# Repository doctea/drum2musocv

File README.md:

# drum2musocv

* Note that I am on the way to replacing this functionality in my system with the [Microlidian](https://github.com/doctea/Microlidian) project instead.

* A USB MIDI interface, originally for adapting the [MidiMuso Orac CV-12](http://midimuso.co.uk/index.php/cv-12/) to be used as a drum machine (mapping GM drum channel/notes and providing triggerable ADSR envelopes), but now with many added features.

* ~~In active development...~~ very likely to be bugs or things that can be very much improved.  Check back for updates or contact me if you're trying to use this!

* Currently targets [Arduino Zero clones](https://www.banggood.com/Geekcreit-SAMD21-M0-Module-32-bit-ARM-Cortex-M0-Core-Development-Board-p-1176168.html)/[Seeeduino Cortex M0+ boards](https://www.seeedstudio.com/Seeeduino-Cortex-M0-p-4070.html), originally started out on an Arduino Uno (probably possible to make it work on a Uno again or other MCUs).

* **Drum pitch mapping** allows you to play the CV-12 using external drum pads, or eg take advantage of FL Studio's note-naming in the piano roll.

* When it isn't receiving an **external clock input**, runs off its own **internal clock** at the last detected BPM.

* Implements **5 triggerable envelopes** (or **9** with two Oracs) with AHDSR (attack, hold, decay, sustain, release) stages, output on the CCs that the midimuso uses for its CV outputs so they can be used as envelopes.  Default mapped to the 'Cymbal Crash 2', 'Cymbal Splash', 'Vibra-slap', 'Ride Bell' and 'Ride Cymbal 1' GM drum notes for input (with MIDI control to map to any of the drum triggers or note-ons on the Harmony/MIDI channels), outputting on the muso's CV outs #1, #2, #3, #4 and #5 respectively (via midimuso CC 1, 7, 11, 71 and 74 - with reconfiguring could be used as triggerable CC envelopes for any device).

* Envelopes can now be set to loop per-envelope ie become freerunning LFOs with envelope-like control.  Retriggerable + inverted mode for each.

* **Visual feedback**: Indicates triggers and envelope levels via a 16-LED RGB Neopixel strip using the FastLED library on pin 9.

* Includes a **control surface preset for FL Studio** to make controlling the general, Euclidian and envelope settings easy and saveable/recallable per-project.

* Has a 19-track **Euclidian rhythm generator** with optional mutation mode, so you can play with your synth without loading a DAW.  Can configure tracks on/off, change mutation settings, etc, from DAW.  In mutation mode, mutates the rhythm every 2 bars, with options on mutation.
 * Could also be used to add generative/mutating Euclidian rhythms to any MIDI device (drum machine etc) if reconfigured to use different output note mappings.

* **Plays bass, chords/arped chords and additional pitched midi channels** from Euclidian patterns, and with **auto-generated chord changes and inversions**.  Allows **tied notes**.
 * If notes are played in via MIDI determine which notes to use for arpeggiation/chords.  Plays chords and additional midi channels with auto-generated chord changes and inversions.

* Plays a **"drum fill"** for the last bar of every phrase by mutating the Euclidian rhythms.

* Temporary hack: uses the pitch bend output instead of the CV output that corresponds to CC 74, because mine seems to be broken.  (could use this in future to add an extra envelope/CV out or LFO output..)

* **Optionally echoes the MIDI output back to the host**, so that you can record the rhythms for re-use or to route to softsynths or other MIDI devices.

* Outputs **4xClock triggers** using a CD74HC4067 multiplexor (5ms latency between outputs if multiple triggered simultaneously) - every beat, every upbeat, every bar, every phrase.  Uses Arduino data pins 2,3,4,5 to set the multiplexor output.

* Can use a single midimuso in mode 0B or 2B, or two midimusos via a midi splitter, one in mode 0B and one in 2A

# Controls

 - Two buttons, button 1 on pin A0 and button 2 on pin 8
 - Press button 1 = cycle through demo modes (standby -> Euclidian -> Euclidian with mutation -> random -> Experimental Euclidian mutation mode that mutates more things and also keeps track of the virtual drummer's limbs to avoid playing impossible rhythms -> back to start)
 - When in a Euclidian mode:
   - Press button 2 = enable/disable Euclidian generation (to shut it up but to keep mode)
   - Hold button 2 for > 2 seconds & release = reset Euclidian patterns to initial default. (LEDs will light up red momentarily)
 - When any button is pressed or released, LEDs will light up violet, current mode indicated by a blue LED on first row of pixels, autoplaying status indicated by red/green on last pixel)

# Routing of features

A diagram to help me understand how everything is routed:-

# Using single midimuso-cv board

  - Configure mode by setting `MUSO_MODE` define in Config.h to `MUSO_MODE_0B` (10xGate, 5xCV Envelope) or `MUSO_MODE_2B` (7xGate, 5xCV Envelope, 2xPitch, 2xPitch Gate)

# Using multiple midimuso-cv boards

  - Configure mode by setting `MUSO_MODE` define in Config.h to `MUSO_MODE_0B_AND_2A` (10xGate, 5xCV Envelope, 2xPitch, 4xPitch Envelope)
  - Now supports running two midimuso-cv boards via MIDI splitter (NOT chained):
    - Board 1 in mode 0B (10 triggers* + 5 envelopes)
    - Board 2 in mode 2A (2 pitch outputs + 4 extended envelopes)
  - Extended envelopes can have parameters set using appropriate CC's on **Channel 11**
    - by default they trigger on notes on MIDI channels 1 + 2 (root pitch / pad pitch)
  - Check the `RELAY_PROGRAM_CHANGE` define in order to enable/protect setting of muso modes when you want to update its mode (allows/prevents program change messages being passed on)
  - *: Because of a problem with the MidiMuso-CV12 in mode 0B (A Gate 1 is also triggered on Channel 1 Pitch input), Kick moves to Stick and Stick is disabled, reducing us to 10 triggers instead of 11.  But does mean the old 'Kick' output can be used as gate for MIDI channel 1.

# MIDI parameters

(TODO: incomplete docs, need to add the notes corresponding to the Muso triggers for bass drum, snare, ch/oh etc, CCs corresponding to the envelope parameters, and other settings eg clock sync)

 - see the [CHANNEL_AND_CC_LIST.txt](CHANNEL_AND_CC_LIST.txt) document for a complete autogenerated list of the existing mappings
 - and [MIDI_CC_TABLE.md](MIDI_CC_TABLE.md) for a slightly better organised autogenerated MIDI CC list

## MIDI Inputs

| MIDI type   | MIDI channel | MIDI number    | Purpose                    |
| ----------  | ------------ | -------------- | -------------------------- | 
| Note on/off | 1,2,3,4      | any            | Output notes to corresponding channel, trigger envelope if assigned |
| Note on/off | 10           | Cymbal Crash 2 | Trigger envelope on CV 1 (default, change by assigning trigger)  |
| Note        | 10           | Cymbal Splash  | Trigger envelope on CV 2 (default, change by assigning trigger)  |
| Note        | 10           | Vibra Slap     | Trigger envelope on CV 3 (default, change by assigning trigger)  |
| Note        | 10           | Ride Bell      | Trigger envelope on CV 4 (default, change by assigning trigger)  |
| Note        | 10           | Ride Cymbal    | Trigger envelope on CV 5* (default, change by assigning trigger)  |
| Note        | 10           | ..GM drums..   | Trigger Muso triggers      |
| CC          | 10           | 32 to 48       | Enable/disable Euclidian track |
| Note+CC etc | 8            | any            | Bass synth - Resend on channel 4 |
| Note        | 9            | any            | Bass synth - Euclidian track arpeggiates held chord on chan 2+3 (see below) |

## MIDI Outputs

| Type         	| MIDI channel | MIDI number   | Purpose |
| ------------- | ------------ | ------------- | ------- |
| Notes/CC/etc  | 1     | any | Output to Muso Pitch 1 |
| Notes/CC/etc  | 2     | any | Output to Muso Pitch 2 |
| Notes/CC/etc  | 3     | any | Output to bitbox keys |
| Notes/CC/etc 	| 4 	| any | Output to bass synth | TODO: forward modulation as aftertouch/velocity/modwheel etc |
| Notes   	| 11    | 36-51 (C2-D#3) | 'shadow' copy of notes sent to midimuso, starting at C2 so they work with default bitbox pads |
| Notes 	| 16 	| 60-70 (C4-?) | outputs to MIDI Muso CV-12, gates for drum triggers |
| CV + pitch 	| 1 	| 1,7,11,71,74+pitch | outputs to MIDI Muso, CV/pitch outputs for envelopes |

* *actually this currently outputs on the Pitch Bend output, as my Muso output seems to be broken - configure this by changing `MUSO_USE_PITCH_FOR` in Drums.h 

# Requirements

 - Use the Seeeduino Zero board profile so that Serial has printf() - install boards from URL https://files.seeedstudio.com/arduino/package_seeeduino_boards_index.json and add contents of the included [boards.txt](boards.txt) to the end of eg `C:\Users\\<YOUR_USERNAME>\AppData\Local\Arduino15\packages\Seeeduino\hardware\sam\1.8.1\boards.txt`.  You can then edit the USB device name and IDs in that file.
 - Can be used in conjunction with USBMidiKlik (https://github.com/TheKikGen/USBMidiKliK) to provide USB MIDI, or can use native USB on boards that support it.  (hasn't been tested on board without native USB for a while so this is likely broken currently)
 - Uses the FortySevenEffects MIDI library and FastLED library (with alternative experimental support for the Adafruit NeoPixel library).
 - Stock DebounceEvent uses delay(), so need to apply patch from https://github.com/arjanmels/debounceevent/commit/c26419a5a2eb83c07bcb69e8073cecd7453c53bf.patch to fix stutter when buttons are pressed

# FL Studio DAW Control Surface preset

 - *Euclidian settings.fst* is an FL Studio Patcher preset for controlling the Euclidian settings (screenshot below).
 - [deprecated] *Drum2MusoCV - Bamblweeny.fst* is an FL Studio MIDI Out preset for controlling the drum triggers and envelope settings - now included in separate tab

# Hardware/demos

[Testing modular + mutating Euclidian sequencer #2 video](https://www.youtube.com/watch?v=taRN2wLEkPA)

 - **TODO:** document the hardware used
  - buttons on which pins / how wired?
  - MIDI DIN on TX, how wired?
  - header output for pixels, how wired?
    - data on pin 9
  - clock outputs, how wired?

----

# Issues

 - Problems with midimuso pitch gates missing note-off messages when stopping everything, when a lot of notes need to be told to go off.  workaround by defining WORKAROUND_MISSED_NOTEOFFS in MidiOutput.hpp to insert short delay()s sometimes when sending a lot of messages during douse_all_trigger() calls.  Tried increasing TX buffer size but makes no difference, this seems to fix things in 99% of cases altho still sometimes misses the messages..
 - Rapidly pressing 'stop' in DAW retriggers notes -- think due to it causing a tick

----

# TODO / future plans + ideas

 - 'Acid' harmony output mode, with note ties and automation acid line generation (maybe take some inspiration from [Aciduino](https://github.com/midilab/aciduino) and [endless acid banger](https://github.com/vitling/acid-banger))

 - Separate the harmony inputs, so you can specify different lines to play for each harmony output, including 'only when note held' stuff

 - Check that chord/scale generation is actually working to produce valid output - wondering if i'm accidentally basing the entire scale off the chord root?

 - Rename the project to something catchier and more reflective of its abilities

 - Refactor to make it easier to add new drum and harmony outputs
   - and modes to re-output drum triggers on appropriate GM Drum notes, for controlling MIDI drum machines (would start at MidiOutput.hpp:fire_trigger and get_muso_pitch_for_trigger for this)

 - Song section mode for song structures, eg build up, break, intense, chilled, ..
   - 'intensity' / 'sparesness' controls over mutation?

 - Different banks of starting rhythms so we don't get bored to tears of 4/4 kick...
   - preprogramme some and have them selectable?
   - or cleverly randomise them somehow like mutations?

 - Replace DebounceEvent library with one that doesn't need patching

 - Make CC config options to able to enable/disable so the CV outputs can be used as CCs, envelopes (done!) or LFOs per-project

 - LFOs

 - TODO: Make euclidian sequences changeable on the fly/configurable, saveable

 - Add more physical buttons to provide greater control over modes  

 - Make a KiCad circuit / PCB / panel to integrate LEDs and outputs behind a panel
   - tiny OLED and rotary encoder would be interesting, to tweak settings from panel without faffing with DAW
   - as would accepting parameter changes via i2c connection from controllers like the [F8R](https://michigansynthworks.com/products/8m-fader-bank-with-cv-i2c-and-midi), like I've just become aware some Eurorack modules do (eg Disting)
 
 - Replace DebounceEvent library with one that doesn't need patching

 - Cut bass by kick option

 - Completely edit euclidian track parameters over MIDI... with feedback to control surface in daw for saving?  Trigger all outputs simultaneously/groups if have two recording groups

 - Shadow triggers with MIDI to trigger Bitbox.  output options - global/per track - muso/bitbox/both.  always/random/alternate/pattern (+euclidian)?  add this to fire_trigger & douse_trigger?
	- more broadly this is turning into a need to have more of a structure for outputs, for sending to host/midi over multiple channels and can be turned on and off easily
	- Allow to configure the octave-shifted melody/pad outputs on Channel 3:
		- configuration of octave shift
		- option to arpeggiate on None / Channel 2 / Channel 3 / Both
		- option to play full-chord / arp / root-only on Channel 3

 - Bitbox recording mode? ie send all triggers necessary to record a sample.  buttons to trigger recording?

 - More 'predictable' random streams... like use 'different' random streams for picking numbers at different stages of mutation, so that can add feature to mutate more tracks simultaneously but keep the existing patterns the same
	- so keep the selection of patterns chosen to change the same, each pattern's mutations the same -- actually not sure if i'm on the right track here.  come back when less tired!

 - More envelope stages (delay?)

 - Other 'modules' to trigger other devices with CV via relays (ie circuit bent stuff).  Extra CVs/triggers direct from the Arduino?  Shitty sample recorder/player?!

 - Hi-hat/crash choke (cut open hat gate when pedal hat is triggered?)

 - Funkier colours / colour blending fx for the pixels

 - Save config options (RGB settings, envelope settings, euclidian patterns etc) to the flash memory and allow configuration via sysex / CCs.
	 - Started adding this, but isn't supported on SAMD platforms, so aborted (untested code remains)
	 - support FRAM over SPI, or saving to SD card?
	 
 - Add extra envelope output on the pitch bend output (but currently using this to replace my broken output C6/cc74)

### Done list

 - Make the envelopes triggerable by any trigger, not just MIDI
	- with toggleables in the control surface using formula conrtoller to combine checkboxes with knob values
 - Can put envelopes into LFO modes: looping and inverted
	- lost ability to modulate from previous version, but looping and inverted is still decent right?  and have run out of ccs to control the envelopes for the envelopes
 - Euclidian fills on last bar of phrase.  Multiply the track parameters to increase/decrease density?
 - Make euclidian sequences work off midi clock, fix any bpm issues.
 - Make BPM guesser only work off the last 4 steps, to handle live changes of tempo better (done, but still needs 3 beats before it becomes accurate...?)
 - Fix problem where BPM guesser doesn't reset when stopped? - done i think
 - Fix problem with lights staying on when sequencer stopped? - seems to be resolved
 - First beat is missing when starting playback.. seems to think it starts from step 1?. -done for both playback and internal, i think !
 - Echo euclidian output back to host so that we can record the midi or reuse it on other instruments etc
 - Better syncing of envelopes to midi clock ?
 - Make modulation configurable per-stage, eg only wobble during release
 - BUG: there is a 'click' at end of envelope releases
 - TODO: find out whether an envelope is being held open or whether the ringing i'm getting is actually a problem with module
 - Not convinced the envelopes are entirely working as intended so need to check & fix this
 - Make modulation sync work again
 - Route MIDI on specfic input channel to specific output channel, so can play eg Neutron through same interface
 - LEDs for indication of mode
 - Shadow triggers with MIDI to trigger Bitbox
   - done: basic shadow of triggers+envelopes on the default bitbox pad trigger notes, sending on channel 11
 - Latency/flam/swing on euclidian tracks.  Adjust the euclidian loop to check a copy of received_ticks that is adjusted by the appropriate latency
        - ie if latency is set to -6, then remove 6 from received_ticks before tests is on bar etc
                - gonna need to restructure slightly for this, or maybe just make some defines for testing like IS_ON_BAR(ticks), IS_ON_STEP(ticks)?
                - will need to turn the loops inside out and iterate over tracks before checking if theyre on beat
 - Set some of the envelopes to act as envelopes synchronous with some of the triggers, for applying modulation to hits or notes.
 - Tied notes, per-track or just for bass.  to do this do we just avoid sending note off for last note until new note has been sent..? off/always/random/pattern?
 - Rough implementation of the melody rhythm randomness from the [endless acid banger](https://github.com/vitling/acid-banger))
 - Make Euclidian bass capable of changing root note / arpeggiate / chord sequences
   - features to do this.  currently arps over held chord
   - make this so can switch between modes...
 - Support multiple MidiMuso-CVs - one for max pitch/cv, one for pitch outputs+envelopes
   - DONE: finish adding control panel for the extra 4 envelopes
     - DONE: added controls for 2 extra envelopes
 
----

# Feedback / Contributions
 
Would love if people found a use for this, so if you are interested at all in this project then it would be great to hear from you!  [Let me know](mailto:doctea@gmail.com) what you're interested in using the project for, what doesn't work, or any other questions or feedback you may have...

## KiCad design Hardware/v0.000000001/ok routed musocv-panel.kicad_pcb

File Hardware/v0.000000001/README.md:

Definitely not to be used!  These are my first attempts at designing a front panel, and a PCB to fit that would host midimuso output jacks alongside RGB LEDs for indication.  Mocked up are spaces for an OLED screen, should I ever manage to get that to work nicely.

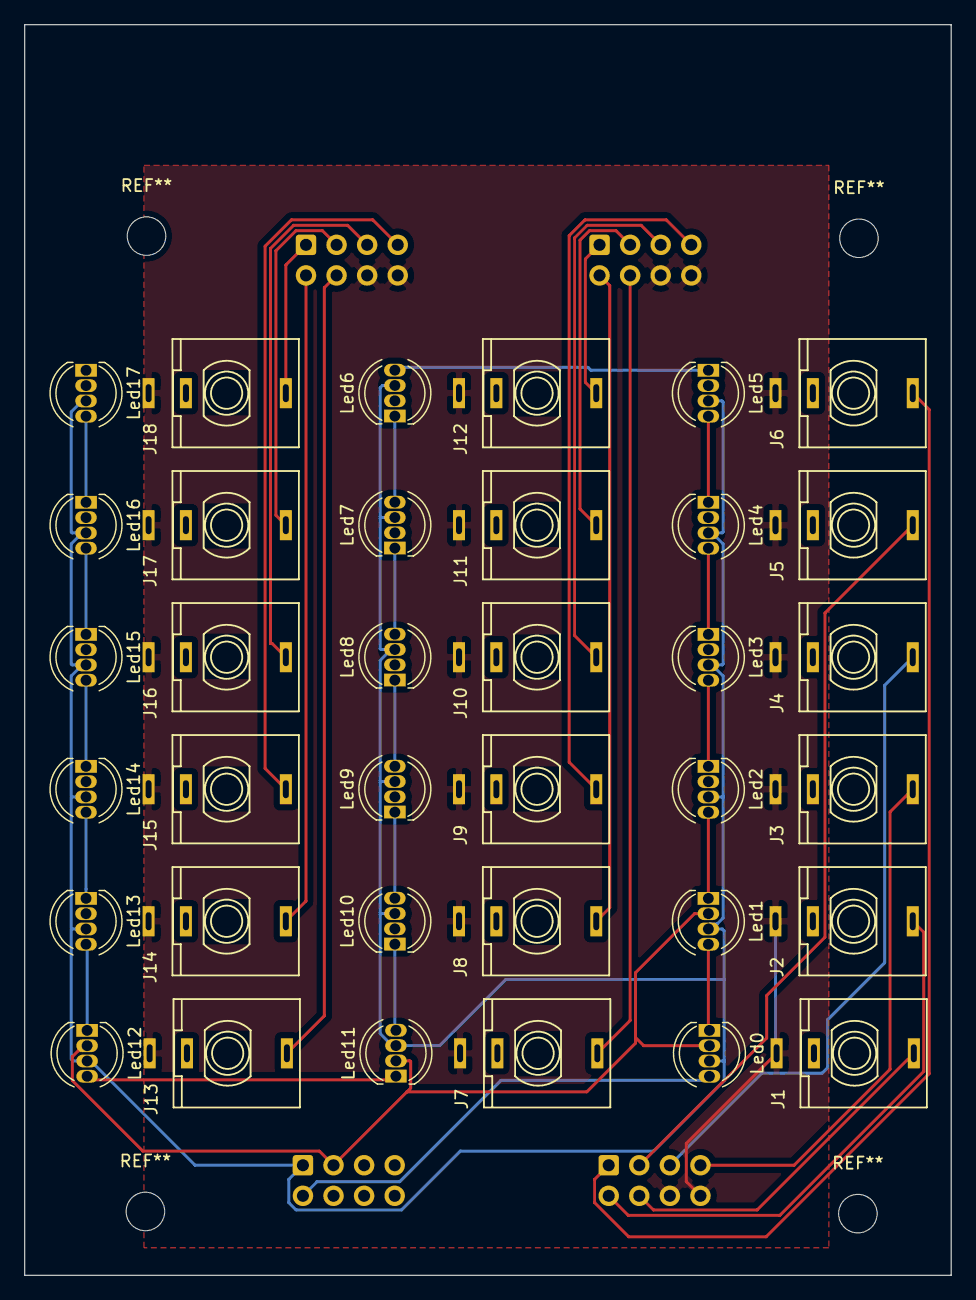
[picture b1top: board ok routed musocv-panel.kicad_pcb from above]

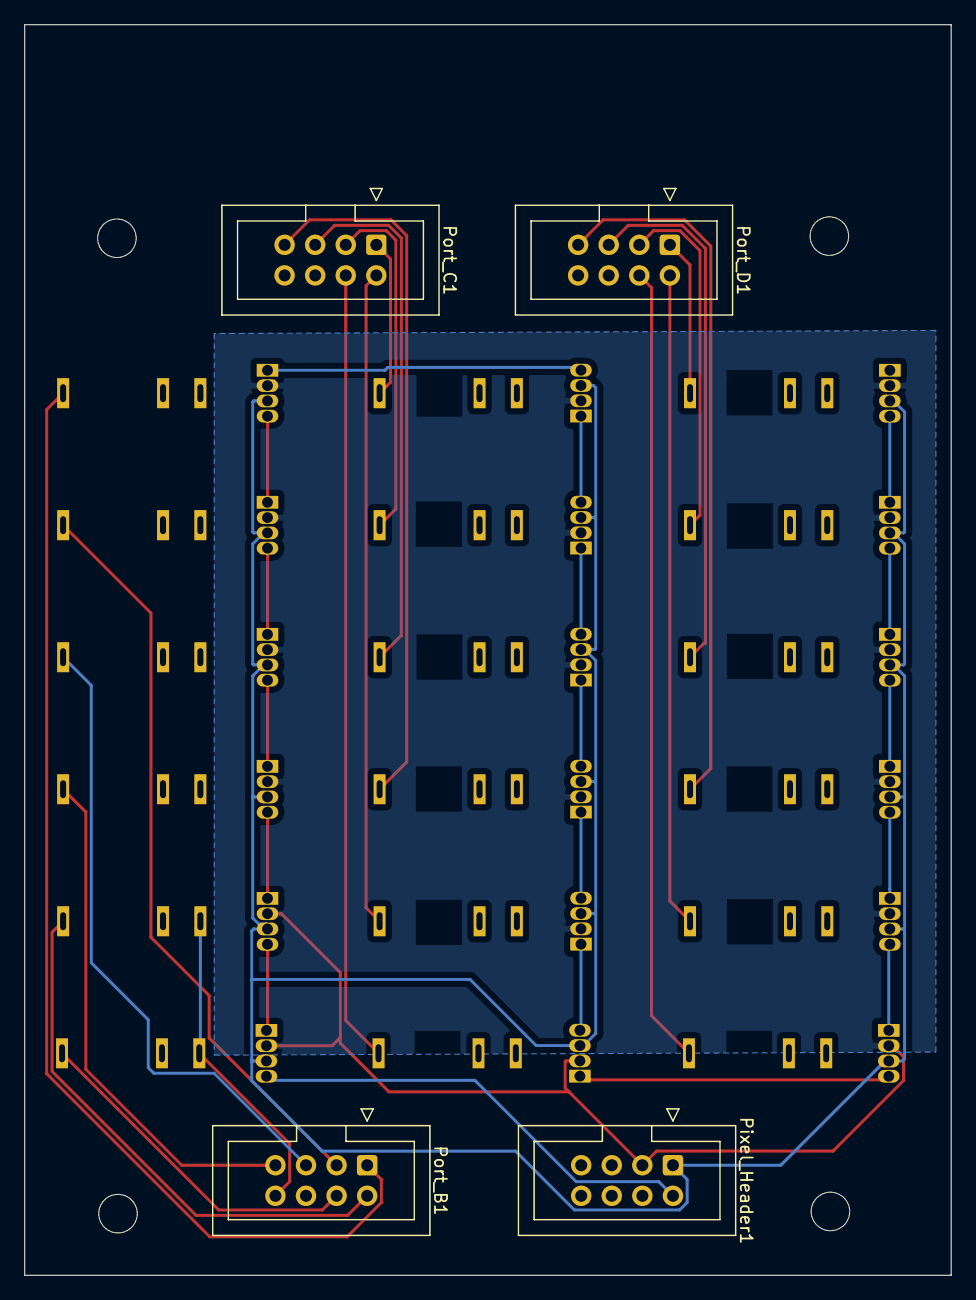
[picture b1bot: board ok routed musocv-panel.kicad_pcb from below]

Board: 2 copper layers, 77.0 x 103.9 mm, 40 parts (4 on the bottom side), 39 nets.

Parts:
J1, J2, J3, J4, J5, J6, J7, J8, J9, J10, J11, J12, J13, J14, J15, J16, J17, J18: fuzzySI_thonkiconn; thonkiconn_fuzzySi
Led0, Led1, Led2, Led3, Led4, Led5, Led6, Led7, Led8, Led9, Led10, Led11, Led12, Led13, Led14, Led15, Led16, Led17: NeoPixel_THT; LED_D5.0mm-4
Pixel_Header1: Conn_02x04_Odd_Even; IDC-Header_2x04_P2.54mm_Vertical
Port_B1: Conn_02x04_Odd_Even; IDC-Header_2x04_P2.54mm_Vertical
Port_C1: Conn_02x04_Odd_Even; IDC-Header_2x04_P2.54mm_Vertical
Port_D1: Conn_02x04_Odd_Even; IDC-Header_2x04_P2.54mm_Vertical

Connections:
GND: J1.1, J2.1, J3.1, J4.1, J5.1, J6.1, J7.1, J8.1, J9.1, J10.1, J11.1, J12.1, J13.1, J14.1, J15.1, J16.1, J17.1, J18.1, Port_B1.6, Port_B1.8, Port_C1.6, Port_C1.8, Port_D1.6, Port_D1.8
unnamed: Led0.1, Led1.4
unnamed: Led1.1, Led2.4
unnamed: Led2.1, Led3.4
unnamed: Led3.1, Led4.4
unnamed: Led4.1, Led5.4
unnamed: Led5.1, Led6.4
unnamed: Led6.1, Led7.4
unnamed: Led7.1, Led8.4
unnamed: Led8.1, Led9.4
unnamed: Led10.1, Led11.4
unnamed: Led9.1, Led10.4
unnamed: Led11.1, Led12.4
unnamed: Led12.1, Led13.4
unnamed: Led13.1, Led14.4
unnamed: Led14.1, Led15.4
unnamed: Led15.1, Led16.4
unnamed: Led16.1, Led17.4
Pixel_Data: Led0.4, Pixel_Header1.2
Pixel_GND: Led0.2, Led1.2, Led2.2, Led3.2, Led4.2, Led5.2, Led6.2, Led7.2, Led8.2, Led9.2, Led10.2, Led11.2, Led12.2, Led13.2, Led14.2, Led15.2, Led16.2, Led17.2, Pixel_Header1.3
Pixel_VDD: Led0.3, Led1.3, Led2.3, Led3.3, Led4.3, Led5.3, Led6.3, Led7.3, Led8.3, Led9.3, Led10.3, Led11.3, Led12.3, Led13.3, Led14.3, Led15.3, Led16.3, Led17.3, Pixel_Header1.1
Port_B_0: J6.3, Port_B1.1
Port_B_1: J5.3, Port_B1.3
Port_B_2: J4.3, Port_B1.5
Port_B_3: J3.3, Port_B1.7
Port_B_4: J2.3, Port_B1.2
Port_B_5: J1.3, Port_B1.4
Port_C_0: J12.3, Port_C1.1
Port_C_1: J11.3, Port_C1.3
Port_C_2: J10.3, Port_C1.5
Port_C_3: J9.3, Port_C1.7
Port_C_4: J8.3, Port_C1.2
Port_C_5: J7.3, Port_C1.4
Port_D_0: J18.3, Port_D1.1
Port_D_1: J17.3, Port_D1.3
Port_D_2: J16.3, Port_D1.5
Port_D_3: J15.3, Port_D1.7
Port_D_4: J14.3, Port_D1.2
Port_D_5: J13.3, Port_D1.4

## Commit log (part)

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2020-08-15 First commit -- after a lot of dumb mistakes and mucking around, actually works to translate the gates in 0X0B mode to general midi channel 10!
2020-08-16 Velocity-sensitive, crude envelope generated on midimuso CC7 when triggered on 57/67 (A4/G5)
2020-08-16 ADSR envelope... non-working at all now heh
2020-08-16 think its bloody working !! commit before proving = tidyup...
2020-08-16 two envelope channels working i think!
2020-08-22 minor fix
2020-08-22 Better define overall MIDI clock sync
2020-08-22 Envelopes seem to be working ok now, maybe some weirdness at times but overall seems good
2020-08-22 tis working better generally, awful bugs fixed, sync lfo isnt quite right tho
2020-09-05 prototype of using a neopixel type strip to indicate activity
2020-09-05 Triggers and envelopes shown on LED strip
2020-09-14 Improved RGB output, added 2 more envelopes, added FL Studio preset to control envelop settings.
2020-09-14 little tidy-up
2020-10-04 don't miss commands when pressing play in daw now -- was neopixel interferring.... made the neopixel update code only update the leds if there has been a change, which seems to have alleviated the pr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
2020-10-08 button on pin A0 to switch in and out of 'demo mode' (triggers random hits, handy for testing synth without loading DAW), moved global variable declarations around
2020-11-20 works on Seeeduino Cortex M0+
2020-11-20 comment
2020-12-29 experimental Euclidian rythym generator and a few other tweaks, need to test this with real midi clock
2020-12-30 WIP, improving clock/bpm handling... syncs with external clock ok, but doesnt track it properly if it is changed. also time when left to its own devices isnt right
2020-12-30 bpm finder works much better, sequences start from correct place
2020-12-30 ignore first false button press + remove some debugging
2020-12-30 better
2021-01-01 envelopes work again, now synced to the new clock internal or external
2021-01-01 tracked missing new UI file for button handling
2021-01-02 clock pulse now sent every beat; slight code tidy up; euclidian pattern XORing (unverified if working like expected!)
2021-01-02 added (and then disabled, because the SAMD platforms dont support it) UNTESTED saving of bpm & patterns to eeprom
2021-01-02 tidy up so that it 'might' work on proper platform
2021-01-02 tidy up and fix a few glitches (all envelopes can be used now, modes are better-behaved when switching between, etc)
2021-01-03 envelopes now work again (even when external clock isn't running...). internal clock now runs when havent had input for a while and continues running even after receiving triggers so that envelopes g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
2021-01-03 attempting to fix envelope sync... currently non-working ...
2021-01-03 ok, that should be envelope rates and stage parameters synced with clock rate solved..! TODO: fix the modulation too
2021-01-09 envelope Sync Ratio Hold-Decay and Sustain-Release now make sense again
2021-01-09 CC control over number of clock ticks it takes to trigger a clock tick, FL DAW template updated to match (CC 111)
2021-01-23 fix silly typo with start/continue handler. change midi handling to omni, in prep for having neutron connected too. tidy up some redundant comments
2021-01-23 hack to use pitch bend output instead of cc74 since mine appears to be broken; pass through channel 8 to channel 2 (for daisychaining my Neutron)
2021-01-27 kill triggers when switching modes, drop default envelope release time to half, cut euclidian note length to half a beat
2021-01-27 internal tidyup to make some things saner
2021-01-30 bass sequence stuff moved into own file, uses defined scale and wraps by octaves correctly. improve serial debugging in Euclidian and Bass (turn on/off with defines)
2021-01-30 fix a couple of things with BPM counter (correct beat / bar numbers)
2021-01-31 more little improvements, need to make the bass options configurable + controllable..
2021-01-31 SLOW via adafruit_gfx library..
2021-01-31 not working too well
2021-02-01 can switch between graphics libs with define
2021-02-05 committed multiple gfx library versions while trying to figure out which is easiest / best
2021-02-06 nonworking or very slow screen attempts
2021-02-06 chords held on midi channel 9 will be arpeggiated on the bass output
2021-02-07 simple rename ahead of making a class out of the channel handler
2021-02-07 tidy up&comment, play bass automatically again, turn off when receiving autobass - need a way to disable it from DAW now
2021-02-08 echo bass notes back to host
2021-02-11 Replace previous Euclidian control surface with a full Patcher preset with MIDI Out configured too
2021-02-11 midi cc's to only play bass when chords held, select arp mode, select demo mode
2021-02-13 fixed file extension
2021-02-13 Euclidian sequences are now song-position dependent, with 127 'banks' to select from
2021-02-14 added more Euclidian mutation options
2021-02-14 explicitly include Euclidian.h, for readability
2021-02-14 more flexible / predictable euclidian seed setting, i think
2021-02-15 CC-switchable mutate mode with a 'total randomise' mode
2021-02-20 stray character
2021-02-20 should be able to have euclidian sequences of more than 16 steps - should be in use on the envelope tracks but might be some bugs there
2021-02-26 typo
2021-02-27 fills only by option, patterns always reset if mutate or fills are enabled, send song start on clock reset, output 24 PPQN MIDI clock
2021-02-27 easier to configure auto arp/progression in code
2021-02-28 extra ideas / docs
2021-02-28 updated diagram
2021-02-28 sort of working harmony refactor, but somehow wrong ChannelState object is being addressed?!
2021-02-28 compiles
2021-03-01 chords playing through melody channel fine
2021-03-01 plays melody using arp over bass playing root, using auto chord progression. still need to refactor the chord progress/arp stuff
2021-03-01 marked readme with what this branch is for
2021-03-07 not really working very well...
2021-03-07 working for 4 clock triggers (downbeat, upbeat, bar, phrase), 5m per trigger, seems working and stable!
2021-03-07 enable/disable by define
2021-03-07 fix clock triggers not triggering
2021-03-12 correct notes played for chord now i think!
2021-03-12 ok think this does play correct notes for chords... (nothing actually changed since last commit?)
2021-03-14 maybe not entirely fixed or sane harmony handling, but much better and several bugs fixed
2021-03-14 some more bugs squashed
2021-03-22 Added some scales, 'improved' inversion logic
2021-03-26 can configure+switch on the fly the midi output channels (also means you can turn them off by setting to 0), melody offset is now one higher than it was before
2021-03-26 added then disabled non-working arping over current chord (need to store this in harmony when triggered and then reuse?)
2021-03-27 euclidian duration 0 douses after a half-step, better kill notes i think?
2021-03-28 force-kill envelope outputs from douse_all_triggers
2021-03-31 stab at supporting midimuso mode 2B, not working as expected, and currently crashes...
2021-04-01 woop i think triggers and everything now match up properly when in 2B mode! todo: sensible program change message handling, ie dont resend same values, to avoid it resetting all the time
2021-04-01 default to NOT relaying program change messages so we dont keep overwriting the midimuso configuration
2021-04-03 2x muso outputs work, doubling up on the bass and melody
2021-04-04 bass and melody now fire from independent Euclidian patterns
2021-04-04 added note that have to use the Seeeduino board config to enable printf on Serial
2021-04-04 couple tidyups
2021-04-05 working a bit better..
2021-04-05 Numerous fixes for vscode intellisense sanity, and general fixes for some things that had broken
2021-04-05 tying notes for porta works..?
2021-04-06 configuiable tie_on for bass output
2021-04-07 default snare pattern is now sane, added screenshot of the current Euclidian settings control panel
2021-04-08 removed a load of redundant commented code etc, moved a few things round
2021-04-10 start of hacky script to build MIDI CC table from the source code
2021-04-10 proper md now?
2021-04-10 update midi cc table builder
2021-04-10 commented CCs
2021-04-11 removed BASS_ARP as can now set arp mode on 2xharmony outputs individually, fixed a problem with note-offs when in chord mode, added workaround for some stuck note on stop failures on midimuso cv-12
2021-04-11 hide some debug
2021-04-14 improve comments and rearranged defines, to make easier to add forthcoming envelope-on-trigger doubling
2021-04-14 tracked .vscode settings (not portable to other setups though presuambly?)
2021-04-15 removed useless file
2021-04-15 untested, should allow per-envelope setting to fire alongside harmony output firing (todo: for pass-thru midi note-on/offs too)
2021-04-18 updated control surface, envelopes kills notes when changing trigger
2021-04-18 updated euclidian settings flstudio control surface again, Envelopes is now on another tab and laid out better
2021-04-18 melody mode and octave offset controls for output#2 (Pad Root)
2021-04-18 improve readme
2021-04-18 link to arduino zero boards
2021-04-20 better direct-midi handling i think?
2021-04-25 mentioned acid-banger again in readme
2021-04-25 use full range of Sustain in envelopes -- allows now to do short blips with envelopes
2021-04-25 just changed colour in daw template
2021-04-29 tracked early fumbles into designing a panel/PCB
2021-05-03 extended envelopes for running multiple midi musos -- one in mode 0B for 11 triggers + 5 envelopes, one in mode 2A for 2 pitches + 4 envelopes
2021-05-03 testing -- better ignore program change messages i think...
2021-05-03 works with two midimusocv boards, configurable envelopes for the pitches, updated images/docs/daw template
2021-05-09 workaround for midimuso-cv12 problem where notes received on channel 1 also trigger the A Gate 1 output when in mode 0B.
2021-05-16 added UI controls for the final two envelopes
2021-05-28 added warning when loop takes longer than one midi tick; disabled some debug output
2021-11-12 optimise gate lookup because why not
2021-11-12 oops, initialise trigger table too
2021-11-13 removed some debug output
2021-11-13 experimental extra modes for lfo mode, inverted and modulated... opens up a new world!
2021-11-27 better handling of out-of-range pitches
2021-11-27 triggers have different led colours and this is refleced in the button colours in the FL template
2021-12-08 default density plays the default pattern as programmed again
2021-12-12 Screen_ada.hpp compiles
2021-12-12 handles envelopes better in both direct midi and euclidian-triggered
2021-12-13 updated docs to explain how the new envelope trigger CCs work
2021-12-13 remove some debug output
2021-12-19 gave the envelopes correct triggers on bootup, made TRIGGER_ defines to make it more obvious whats going on
2021-12-21 experimental mutate density option (on by default). cleaned up cc list
2021-12-21 fixed patcher preset so its not in edit mode when it opens
2021-12-26 profiling to try and find the WARN_PERF error that went away when i upped bpm anyway??? and experimental demo_mode 4 that mutates the root pitch
2021-12-28 profiling / minor tidy up
2021-12-29 DUHHH fixed stupid variable rename that broke octaves
2021-12-30 reverted playing flag and rotation code again, as still not sure that works. midi clock now counts as input -- this seems to be required to make this work with Ableton properly - guess FL must be sen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
2022-01-01 limb-tracking in experimental euclidian mode (don't fire triggers if limb has already been used); reverted last_input_at/last_tick_at test so that works when playing from DAW again..
2022-01-01 should compile
2022-01-01 removed bad files
2022-01-01 display works and shows time to update display - still unusable at 36ms. ssd1306
2022-02-20 used for live
2022-02-26 fixed default pulse per clock in template
2022-02-27 seems to stay in sync better now...?
2022-05-02 hmmm doesnt throw errors in my current vscode environment anymore -- tracked some minor(?) changes -- uncertain if this will actually compile / if it is working version though
2022-07-09 hooray, compiles
2022-09-10 bloody thing compiles now
